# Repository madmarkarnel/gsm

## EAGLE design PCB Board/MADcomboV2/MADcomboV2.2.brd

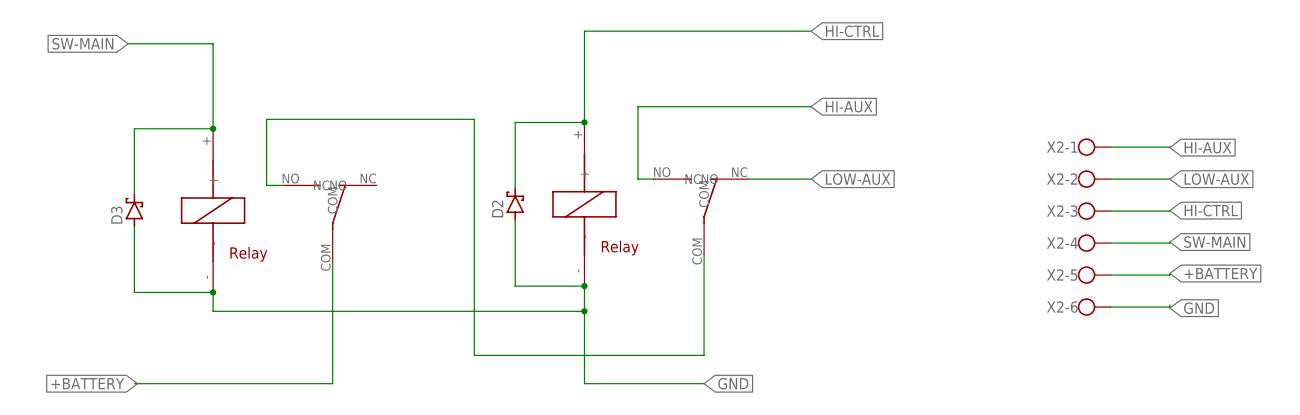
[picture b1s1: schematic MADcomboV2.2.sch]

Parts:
D2, D3: SCHOTTKY-DIODESMD; SMB
U$3, U$4: RELAY_MINI_SONGLE
X2: W237-136

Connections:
+BATTERY: U$3.COM, X2.5
GND: D2.A, D3.A, U$3.-, U$4.-, X2.6
HI-AUX: U$4.NO, X2.1
HI-CTRL: D2.C, U$4.+, X2.3
LOW-AUX: U$4.NC, X2.2
unnamed: U$3.NO, U$4.COM
SW-MAIN: D3.C, U$3.+, X2.4

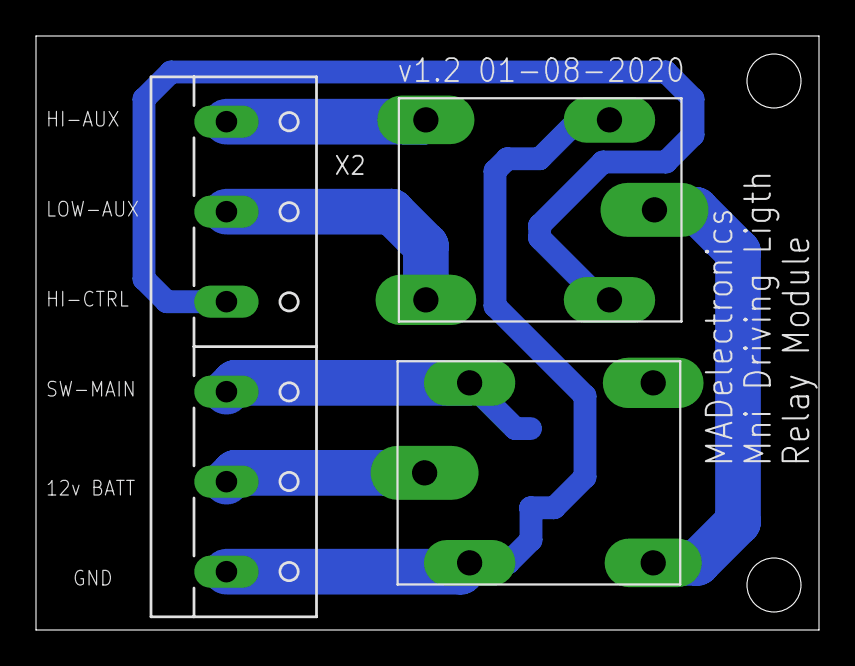
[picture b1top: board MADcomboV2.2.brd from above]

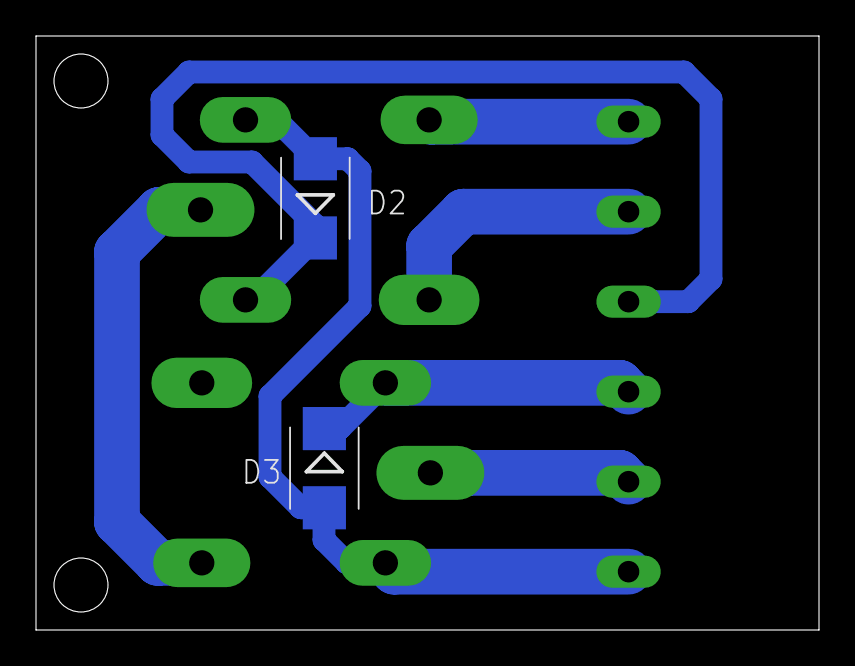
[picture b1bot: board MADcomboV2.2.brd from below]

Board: 2 copper layers, 43.5 x 33.0 mm, 6 parts (3 on the bottom side), 7 nets.

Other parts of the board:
U$2: MADTRONICS_LOGO_6MM

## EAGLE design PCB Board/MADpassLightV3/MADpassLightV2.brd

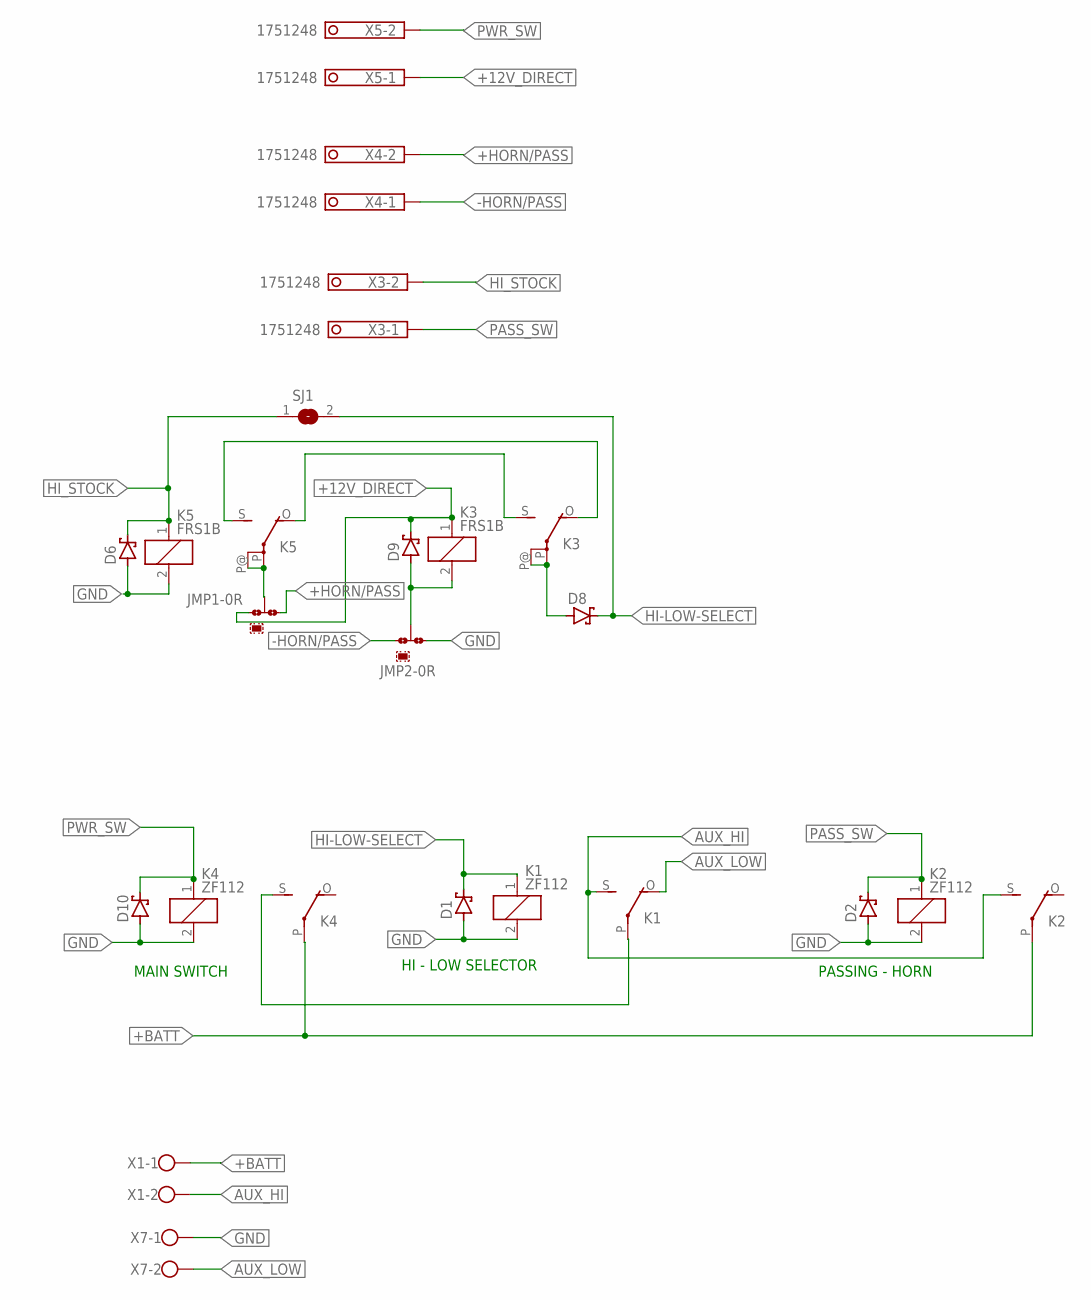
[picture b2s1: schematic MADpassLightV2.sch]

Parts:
D1, D2, D6, D8, D9, D10: SCHOTTKY-DIODESMD; SMB
JMP1, JMP2: 0R-JUMPA; A0R-JMP
K1, K2, K4: ZF112
K3, K5: FRS1B
SJ1: SJ
X1, X7: W237-102
X3, X4, X5: 1751248

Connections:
+12V_DIRECT: D9.C, JMP1.1, K3.1, X5.1
+BATT: K2.P, K4.P, X1.1
+HORN/PASS: JMP1.3, X4.2
-HORN/PASS: JMP2.1, X4.1
AUX: D8.A, K3.P, K3.P@
AUX_HI: K1.S, K2.S, X1.2
AUX_LOW: K1.O, X7.2
GND: D1.A, D2.A, D6.A, D10.A, JMP2.3, K1.2, K2.2, K4.2, K5.2, X7.1
HI-LOW-SELECT: D1.C, D8.C, K1.1, SJ1.2
HI_STOCK: D6.C, K5.1, SJ1.1, X3.2
unnamed: K1.P, K4.S
unnamed: K3.S, K5.O
unnamed: D9.A, JMP2.2, K3.2
unnamed: JMP1.2, K5.P, K5.P@
unnamed: K3.O, K5.S
PASS_SW: D2.C, K2.1, X3.1
PWR_SW: D10.C, K4.1, X5.2

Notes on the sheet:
MAIN SWITCH
HI - LOW SELECTOR
PASSING - HORN

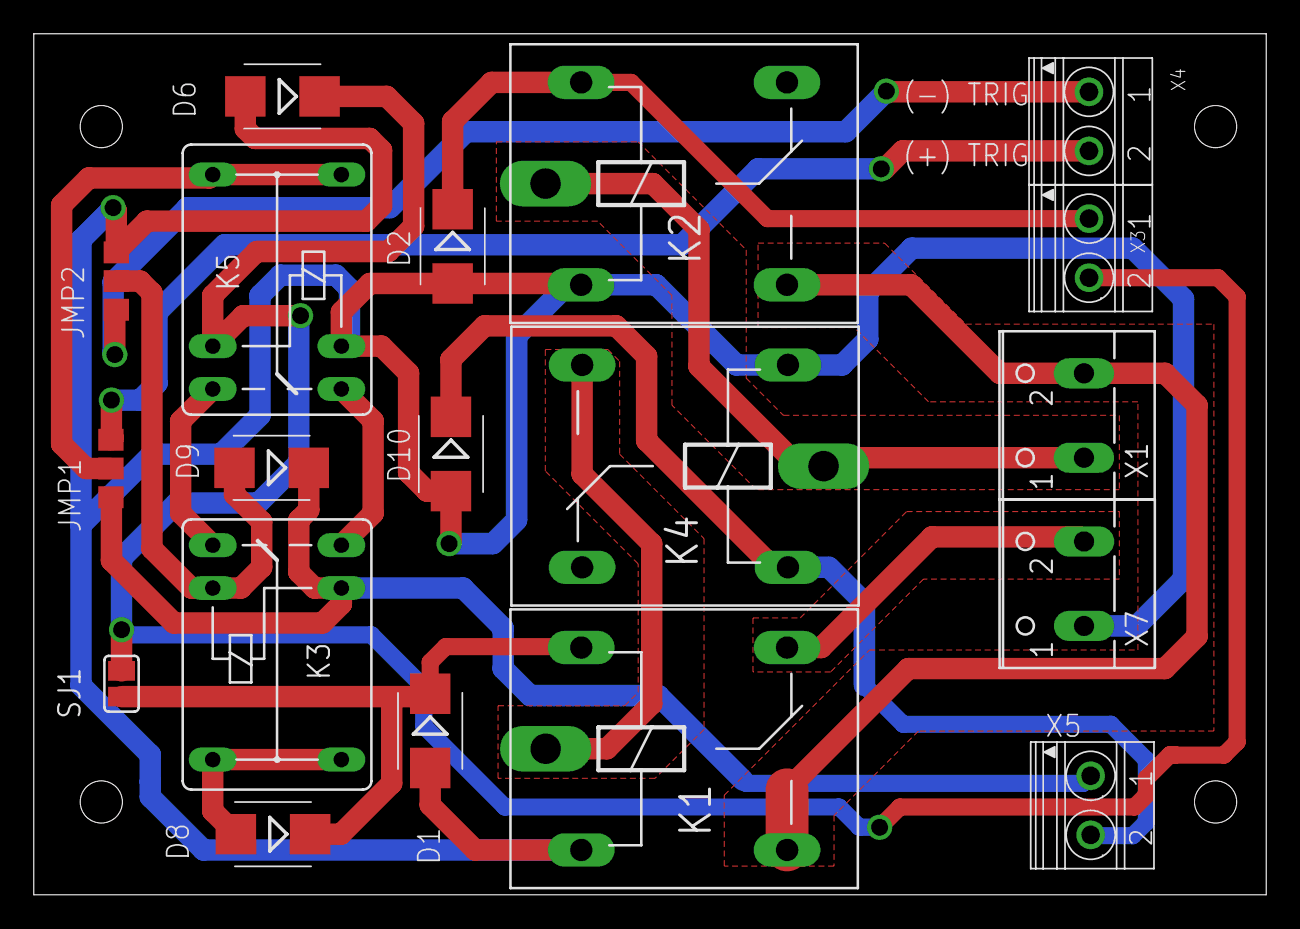
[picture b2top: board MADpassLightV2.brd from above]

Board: 2 copper layers, 73.0 x 51.0 mm, 19 parts (0 on the bottom side), 17 nets.

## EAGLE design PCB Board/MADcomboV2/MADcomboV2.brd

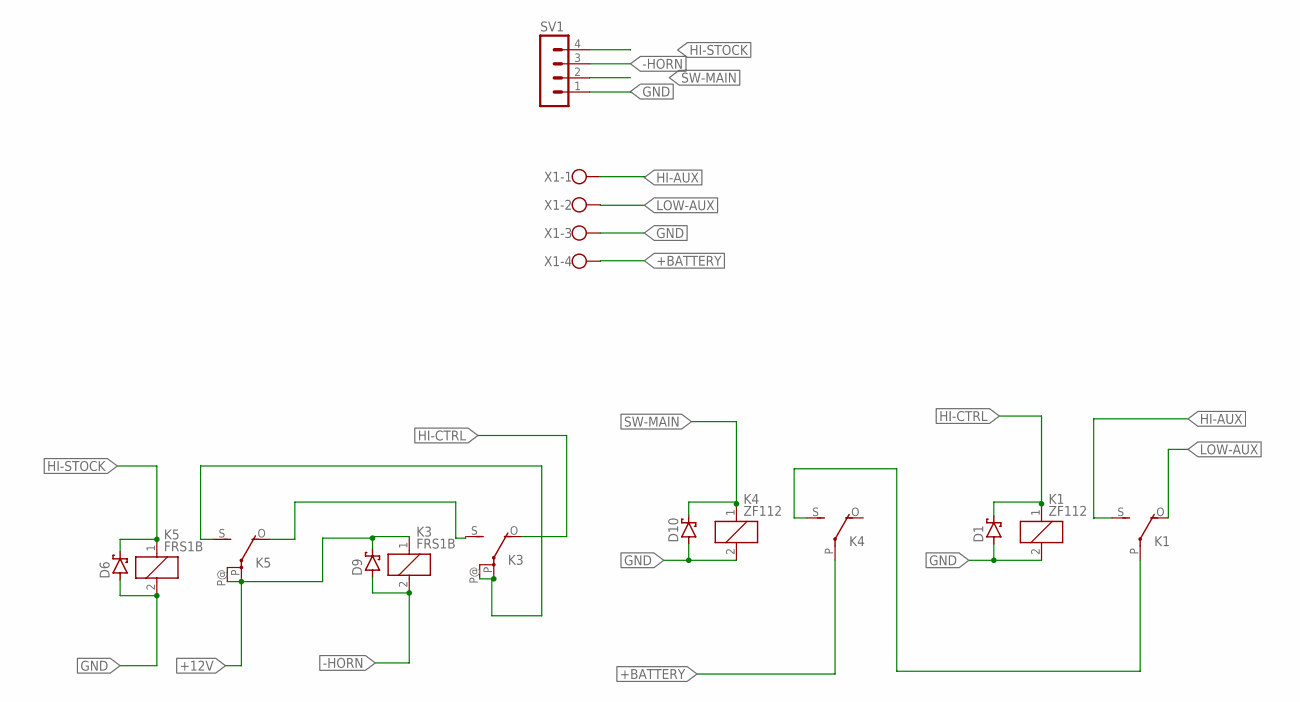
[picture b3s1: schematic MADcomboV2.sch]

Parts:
D1, D6, D9, D10: SCHOTTKY-DIODESMD; SMB
K1, K4: ZF112
K3, K5: FRS1B
SV1: MA04-1
X1: W237-4

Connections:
+12V: D9.C, K3.1, K5.P, K5.P@
+BATTERY: K4.P, X1.4
-HORN: D9.A, K3.2, SV1.3
GND: D1.A, D6.A, D10.A, K1.2, K4.2, K5.2, SV1.1, X1.3
HI-AUX: K1.S, X1.1
HI-CTRL: D1.C, K1.1, K3.O
HI-STOCK: D6.C, K5.1, SV1.4
LOW-AUX: K1.O, X1.2
unnamed: K3.P, K3.P@, K5.S
unnamed: K3.S, K5.O
unnamed: K1.P, K4.S
SW-MAIN: D10.C, K4.1, SV1.2

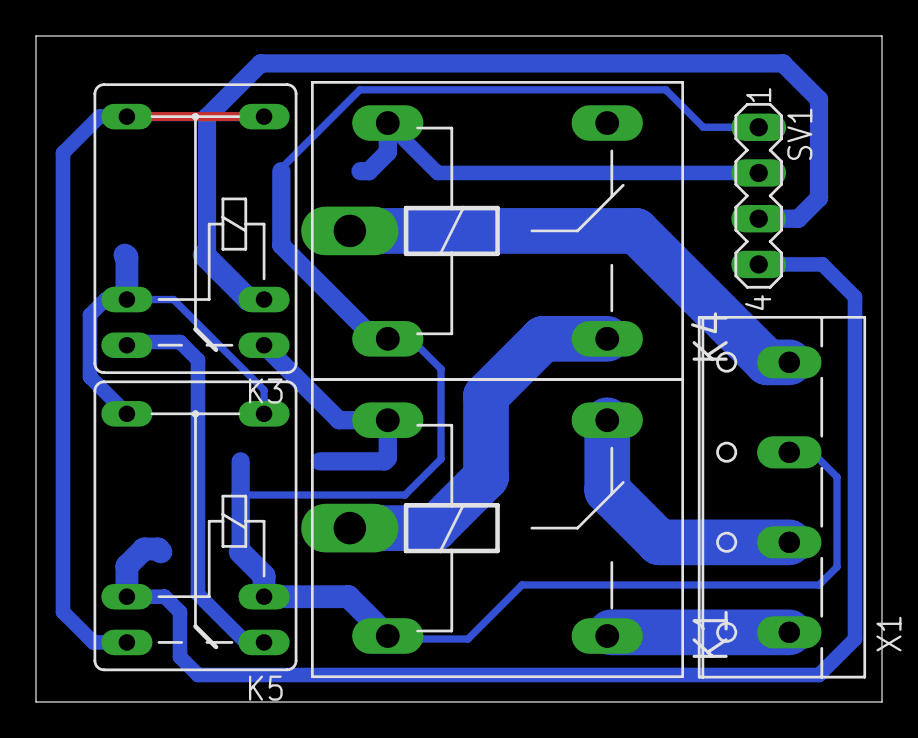
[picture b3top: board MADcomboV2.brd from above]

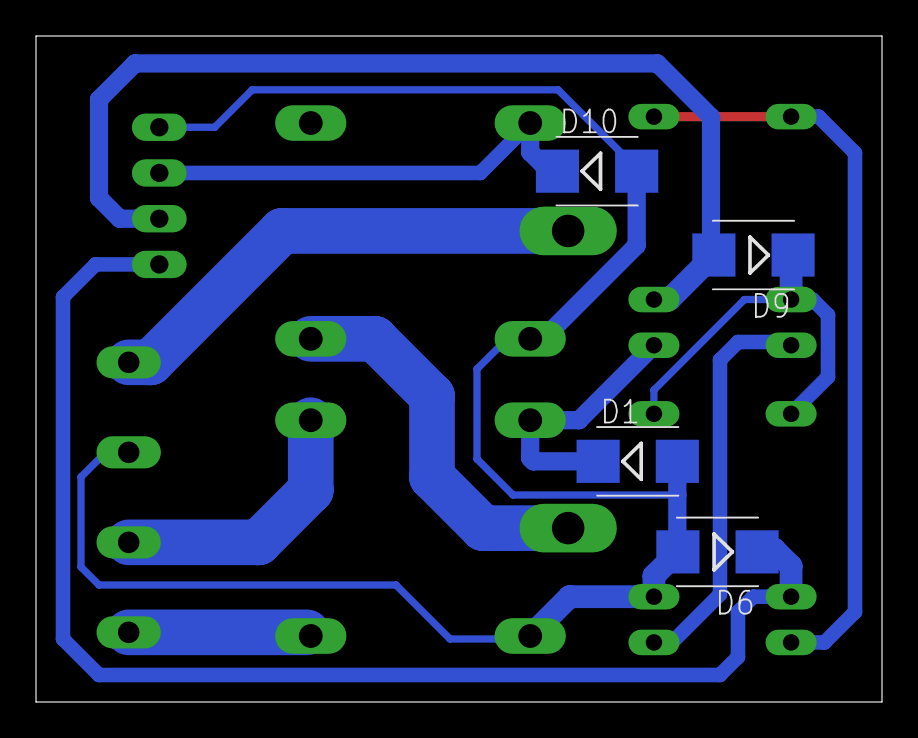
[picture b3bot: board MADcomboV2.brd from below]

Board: 2 copper layers, 47.0 x 37.0 mm, 10 parts (4 on the bottom side), 12 nets.

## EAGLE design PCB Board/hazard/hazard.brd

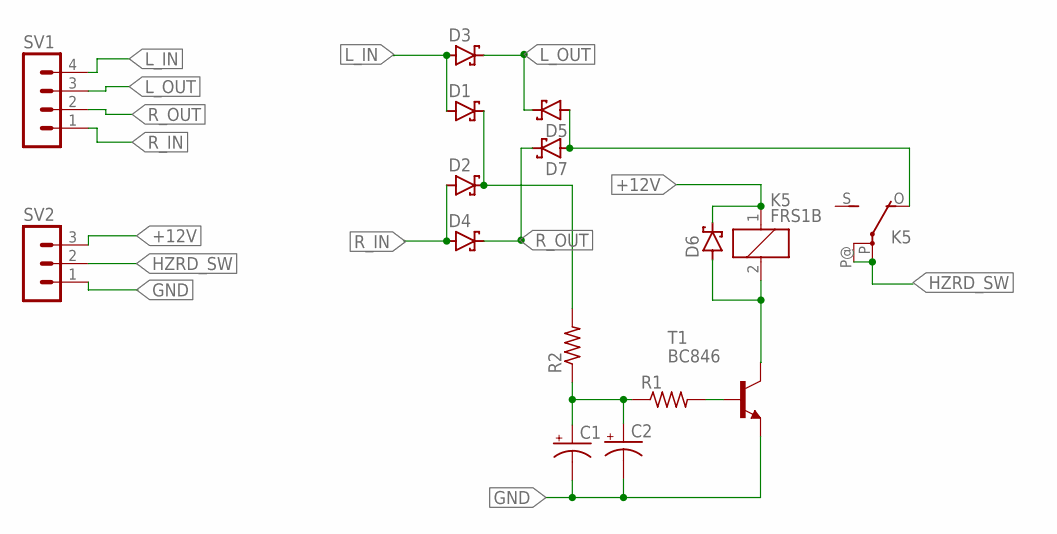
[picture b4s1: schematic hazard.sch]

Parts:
C1, C2: CPOL-USE1.8-4; E1,8-4
D1, D2, D3, D4, D5, D6, D7: SCHOTTKY-DIODESMD; SMB
K5: FRS1B
R1, R2: R-US_R0603; R0603
SV1: MA04-1
SV2: MA03-1
T1: BC846; SOT23

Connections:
+12V: D6.C, K5.1, SV2.3
GND: C1.-, C2.-, SV2.1, T1.2 (E)
HZRD_SW: K5.P, K5.P@, SV2.2
L_IN: D1.A, D3.A, SV1.4
L_OUT: D3.C, D5.C, SV1.3
unnamed: D5.A, D7.A, K5.O
unnamed: D6.A, K5.2, T1.3 (C)
unnamed: R1.2, T1.1 (B)
unnamed: C1.+, C2.+, R1.1, R2.1
unnamed: D1.C, D2.C, R2.2
R_IN: D2.A, D4.A, SV1.1
R_OUT: D4.C, D7.C, SV1.2

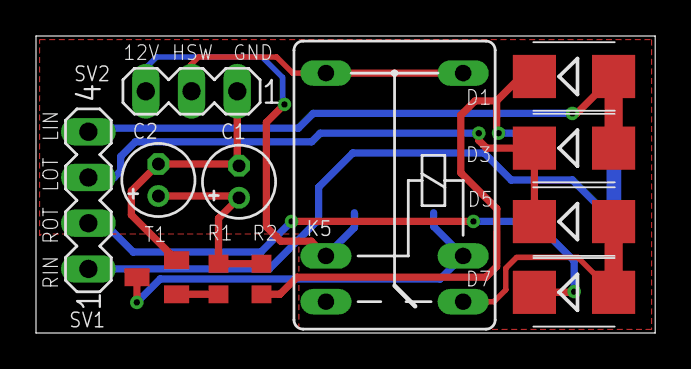
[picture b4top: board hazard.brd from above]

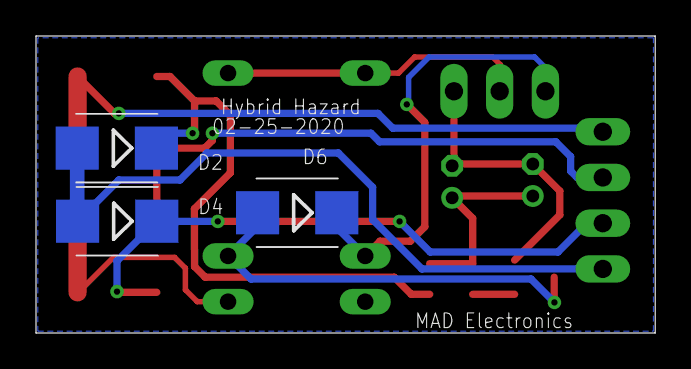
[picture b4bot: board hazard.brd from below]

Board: 2 copper layers, 34.4 x 16.5 mm, 15 parts (3 on the bottom side), 12 nets.

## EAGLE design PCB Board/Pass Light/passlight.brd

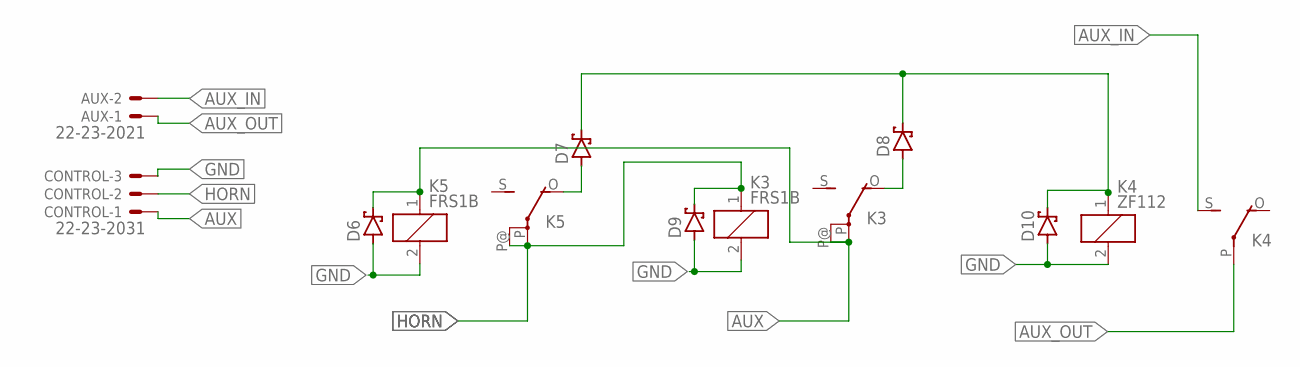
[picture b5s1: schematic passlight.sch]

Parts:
AUX: 22-23-2021
CONTROL: 22-23-2031
D6, D7, D8, D9, D10: SCHOTTKY-DIODESMD; SMB
K3, K5: FRS1B
K4: ZF112

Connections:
AUX: CONTROL.1, D6.C, K3.P, K3.P@, K5.1
AUX_IN: AUX.2, K4.S
AUX_OUT: AUX.1, K4.P
GND: CONTROL.3, D6.A, D9.A, D10.A, K3.2, K4.2, K5.2
HORN: CONTROL.2, D9.C, K3.1, K5.P, K5.P@
unnamed: D7.A, K5.O
unnamed: D8.A, K3.O
unnamed: D7.C, D8.C, D10.C, K4.1

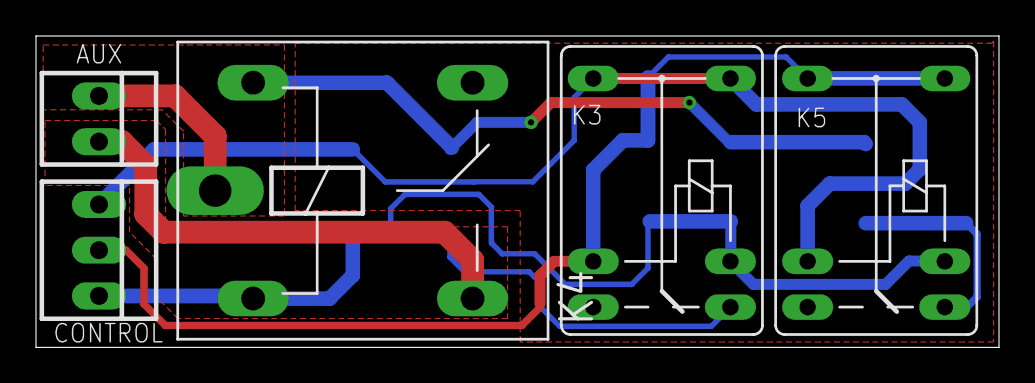
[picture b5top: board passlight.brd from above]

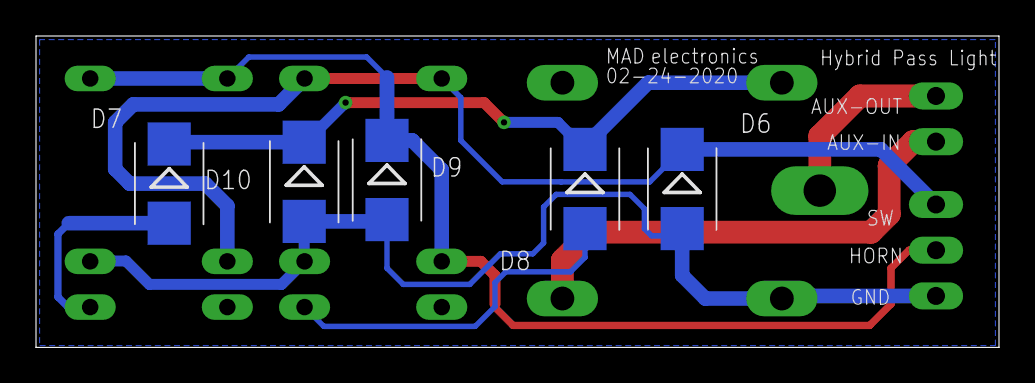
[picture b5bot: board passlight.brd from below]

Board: 2 copper layers, 53.5 x 17.3 mm, 10 parts (5 on the bottom side), 8 nets.

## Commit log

2020-02-18 testing pins
2020-02-18 hazard
2020-02-24 pcb board
2020-02-24 Hybrid hazard
2020-07-04 version 2 MAD combo combo power switch for function witch combo
2020-07-05 updated combo light
2020-07-09 MADpasslight V3
2020-08-01 Mini Driving Light Relay Module
2020-09-16 BLDC_controller
2020-09-16 Added wireless gamepad transmitter
